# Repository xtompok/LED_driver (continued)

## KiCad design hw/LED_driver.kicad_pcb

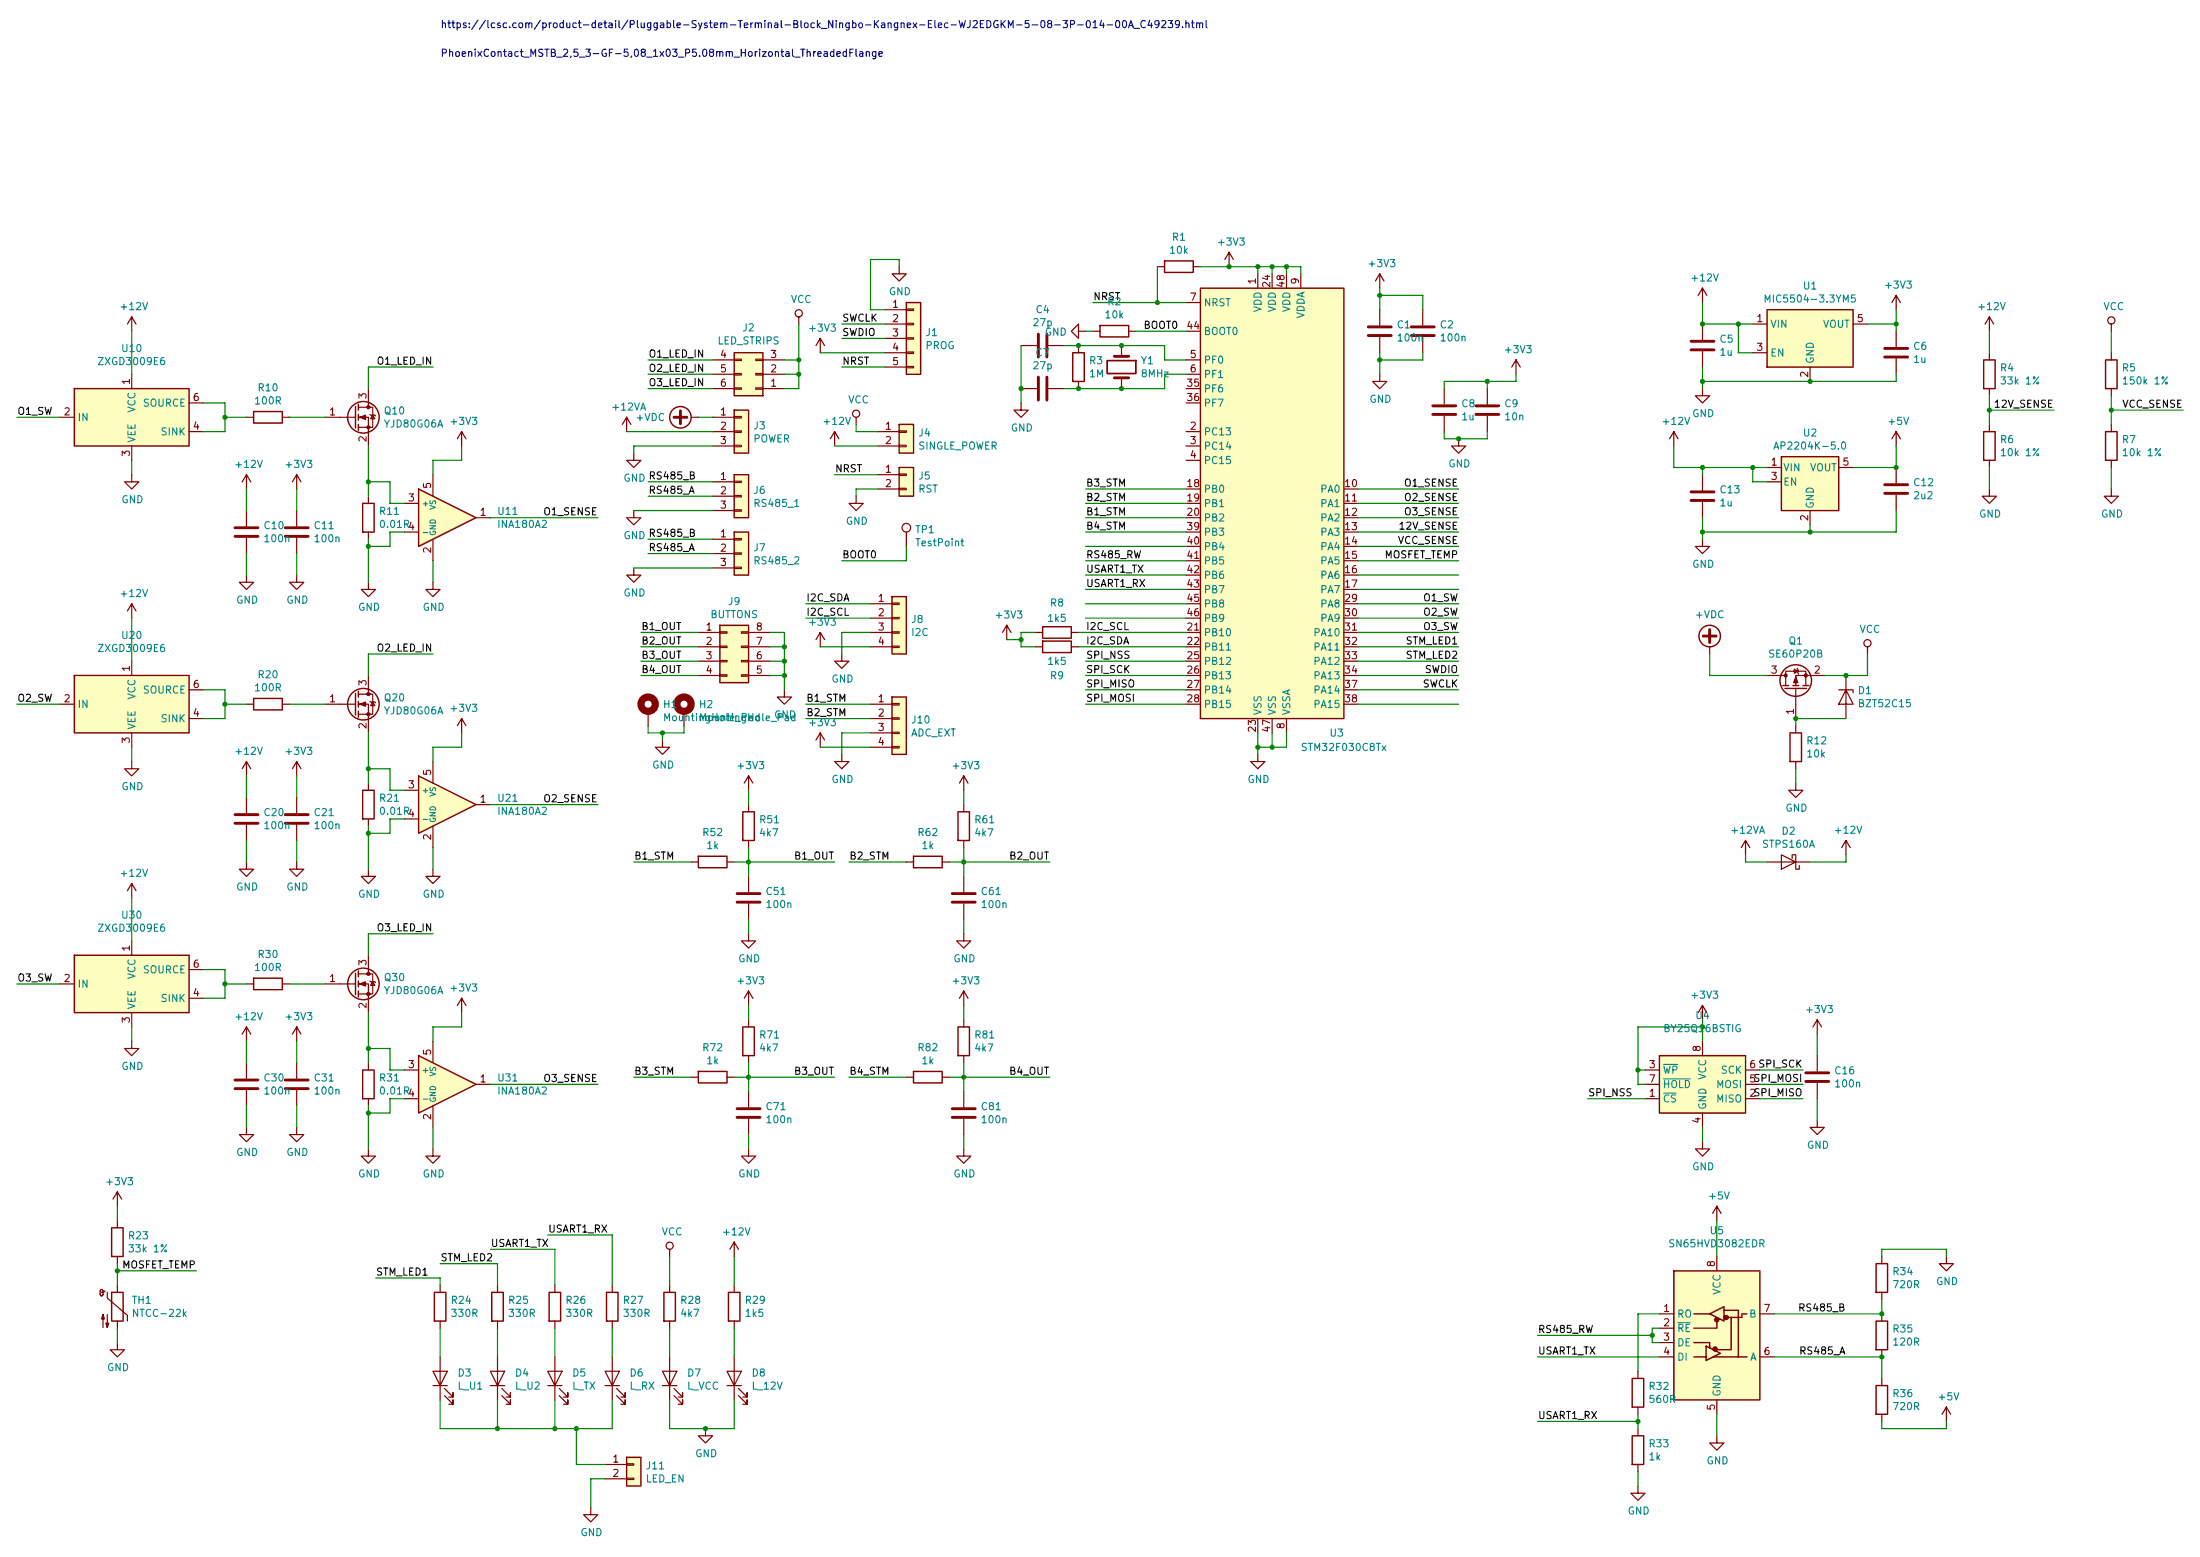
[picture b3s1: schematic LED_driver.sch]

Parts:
C1, C2, C10, C11, C16, C20, C21, C30, C31, C51, C61, C71, C81: 100n; C_0603_1608Metric
C4, C7: 27p; C_0603_1608Metric
C5, C6, C8, C13: 1u; C_0603_1608Metric
C9: 10n; C_0603_1608Metric
C12: 2u2; C_0603_1608Metric
D1: BZT52C15; D_SOD-123F
D2: STPS160A; D_SMA
D3: L_U1; LED_PLCC-2
D4: L_U2; LED_PLCC-2
D5: L_TX; LED_PLCC-2
D6: L_RX; LED_PLCC-2
D7: L_VCC; LED_PLCC-2
D8: L_12V; LED_PLCC-2
H1, H2: MountingHole_Pad; MountingHole_3.2mm_M3_Pad_Via
J1: PROG; Molex_KK-254_AE-6410-05A_1x05_P2.54mm_Vertical
J2: LED_STRIPS; Molex_Micro-Fit_3.0_43045-0600_2x03_P3.00mm_Horizontal
J3: POWER; PhoenixContact_MSTB_2,5_3-GF-5,08_1x03_P5.08mm_Horizontal_T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
J4: SINGLE_POWER; PinHeader_1x02_P2.54mm_Vertical
J5: RST; PinHeader_1x02_P2.54mm_Vertical
J6: RS485_1; PTSA_1.5_3-3.5-Z_1985205
J7: RS485_2; PTSA_1.5_3-3.5-Z_1985205
J8: I2C; Molex_KK-254_AE-6410-04A_1x04_P2.54mm_Vertical
J9: BUTTONS; Molex_Micro-Fit_3.0_43045-0800_2x04_P3.00mm_Horizontal
J10: ADC_EXT; Molex_KK-254_AE-6410-04A_1x04_P2.54mm_Vertical
J11: LED_EN; PinHeader_1x02_P2.54mm_Vertical
Q1: SE60P20B; TO-252-2
Q10, Q20, Q30: YJD80G06A; TO-252-2
R1, R2, R12: 10k; R_0603_1608Metric
R3: 1M; R_0603_1608Metric
R4, R23: 33k 1%; R_0603_1608Metric
R5: 150k 1%; R_0603_1608Metric
R6, R7: 10k 1%; R_0603_1608Metric
R8, R9, R29: 1k5; R_0603_1608Metric
R10, R20, R30: 100R; R_0603_1608Metric
R11, R21, R31: 0.01R; R_1206_3216Metric
R24, R25, R26, R27: 330R; R_0603_1608Metric
R28, R51, R61, R71, R81: 4k7; R_0603_1608Metric
R32: 560R; R_0603_1608Metric
R33, R52, R62, R72, R82: 1k; R_0603_1608Metric
R34, R36: 720R; R_0603_1608Metric
R35: 120R; R_0603_1608Metric
TH1: NTCC-22k; C_Disc_D3.8mm_W2.6mm_P2.50mm
TP1: TestPoint; TestPoint_THTPad_D2.0mm_Drill1.0mm
U1: MIC5504-3.3YM5; SOT-23-5
U2: AP2204K-5.0; SOT-23-5
U3: STM32F030C8Tx; LQFP-48_7x7mm_P0.5mm
U4: BY25Q16BSTIG; SOP-8_3.9x4.9mm_P1.27mm
U5: SN65HVD3082EDR; SOP-8_3.9x4.9mm_P1.27mm
U10, U20, U30: ZXGD3009E6; SOT-23-6
U11, U21, U31: INA180A2; SOT-23-5
Y1: 8MHz; Crystal_HC49-U_Vertical

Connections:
+3V3: C1.1, C2.1, C6.1, C8.1, C9.1, C11.1, C16.1, C21.1, C31.1, J1.4, J8.4, J10.4, R1.1, R8.2, R9.2, R23.1, R51.1, R61.1, R71.1, R81.1, U1.5 (VOUT), U3.1 (VDD), U3.9 (VDDA), U3.24 (VDD), U3.48 (VDD), U4.3 (~WP), U4.7 (~HOLD), U4.8 (VCC), U11.5 (VS), U21.5 (VS), U31.5 (VS)
+5V: C12.1, R36.2, U2.5 (VOUT), U5.8 (VCC)
+12V: C5.1, C10.1, C13.1, C20.1, C30.1, D2.1 (K), J4.2, R4.1, R29.1, U1.1 (VIN), U1.3 (EN), U2.1 (VIN), U2.3 (EN), U10.1 (VCC), U20.1 (VCC), U30.1 (VCC)
+12VA: D2.2 (A), J3.2
+VDC: J3.1, Q1.3 (D)
/12V_SENSE: R4.2, R6.1, U3.13 (PA3)
/B1_OUT: C51.1, J9.1, R51.2, R52.1
/B1_STM: J10.1, R52.2, U3.20 (PB2)
/B2_OUT: C61.1, J9.2, R61.2, R62.1
/B2_STM: J10.2, R62.2, U3.19 (PB1)
/B3_OUT: C71.1, J9.3, R71.2, R72.1
/B3_STM: R72.2, U3.18 (PB0)
/B4_OUT: C81.1, J9.4, R81.2, R82.1
/B4_STM: R82.2, U3.39 (PB3)
/BOOT0: R2.1, TP1.1, U3.44 (BOOT0)
/I2C_SCL: J8.2, R8.1, U3.21 (PB10)
/I2C_SDA: J8.1, R9.1, U3.22 (PB11)
/MOSFET_TEMP: R23.2, TH1.1, U3.15 (PA5)
/NRST: J1.5, J5.1, R1.2, U3.7 (NRST)
/O1_LED_IN: J2.4, Q10.3 (D)
/O1_SENSE: U3.10 (PA0), U11.1
/O1_SW: U3.29 (PA8), U10.2 (IN)
/O2_LED_IN: J2.5, Q20.3 (D)
/O2_SENSE: U3.11 (PA1), U21.1
/O2_SW: U3.30 (PA9), U20.2 (IN)
/O3_LED_IN: J2.6, Q30.3 (D)
/O3_SENSE: U3.12 (PA2), U31.1
/O3_SW: U3.31 (PA10), U30.2 (IN)
/RS485_A: J6.2, J7.2, R35.2, R36.1, U5.6 (A)
/RS485_B: J6.1, J7.1, R34.2, R35.1, U5.7 (B)
/RS485_RW: U3.41 (PB5), U5.2 (~RE), U5.3 (DE)
/SPI_MISO: U3.27 (PB14), U4.2 (MISO)
/SPI_MOSI: U3.28 (PB15), U4.5 (MOSI)
/SPI_NSS: U3.25 (PB12), U4.1 (~CS)
/SPI_SCK: U3.26 (PB13), U4.6 (SCK)
/STM_LED1: R24.1, U3.32 (PA11)
/STM_LED2: R25.1, U3.33 (PA12)
/SWCLK: J1.2, U3.37 (PA14)
/SWDIO: J1.3, U3.34 (PA13)
/USART1_RX: R27.1, R32.2, R33.1, U3.43 (PB7)
/USART1_TX: R26.1, U3.42 (PB6), U5.4 (DI)
/VCC_SENSE: R5.2, R7.1, U3.14 (PA4)
GND: C1.2, C2.2, C4.2, C5.2, C6.2, C7.2, C8.2, C9.2, C10.2, C11.2, C12.2, C13.2, C16.2, C20.2, C21.2, C30.2, C31.2, C51.2, C61.2, C71.2, C81.2, D7.1 (K), D8.1 (K), H1.1, H2.1, J1.1, J3.3, J5.2, J6.3, J7.3, J8.3, J9.5, J9.6, J9.7, J9.8, J10.3, J11.2, R2.2, R6.2, R7.2, R11.2, R12.2, R21.2, R31.2, R33.2, R34.1, TH1.2, U1.2 (GND), U2.2 (GND), U3.8 (VSSA), U3.23 (VSS), U3.47 (VSS), U4.4 (GND), U5.5 (GND), U10.3 (VEE), U11.2 (GND), U11.4 (-), U20.3 (VEE), U21.2 (GND), U21.4 (-), U30.3 (VEE), U31.2 (GND), U31.4 (-)
unnamed: C4.1, R3.1, U3.5 (PF0), Y1.1
unnamed: C7.1, R3.2, U3.6 (PF1), Y1.2
unnamed: D1.2 (A), Q1.1 (G), R12.1
unnamed: D3.1 (K), D4.1 (K), D5.1 (K), D6.1 (K), J11.1
unnamed: D3.2 (A), R24.2
unnamed: D4.2 (A), R25.2
unnamed: D5.2 (A), R26.2
unnamed: D6.2 (A), R27.2
unnamed: D7.2 (A), R28.2
unnamed: D8.2 (A), R29.2
unnamed: Q10.1 (G), R10.1
unnamed: Q10.2 (S), R11.1, U11.3 (+)
unnamed: Q20.1 (G), R20.1
unnamed: Q20.2 (S), R21.1, U21.3 (+)
unnamed: Q30.1 (G), R30.1
unnamed: Q30.2 (S), R31.1, U31.3 (+)
unnamed: R10.2, U10.4 (SINK), U10.6 (SOURCE)
unnamed: R20.2, U20.4 (SINK), U20.6 (SOURCE)
unnamed: R30.2, U30.4 (SINK), U30.6 (SOURCE)
unnamed: R32.1, U5.1 (RO)
VCC: D1.1 (K), J2.1, J2.2, J2.3, J4.1, Q1.2 (S), R5.1, R28.1

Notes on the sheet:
https://lcsc.com/product-detail/Pluggable-System-Terminal-Block_Ningbo-Kangnex-Elec-WJ2EDGKM-5-08-3P-014-00A_C49239.html
PhoenixContact_MSTB_2,5_3-GF-5,08_1x03_P5.08mm_Horizontal_ThreadedFlange

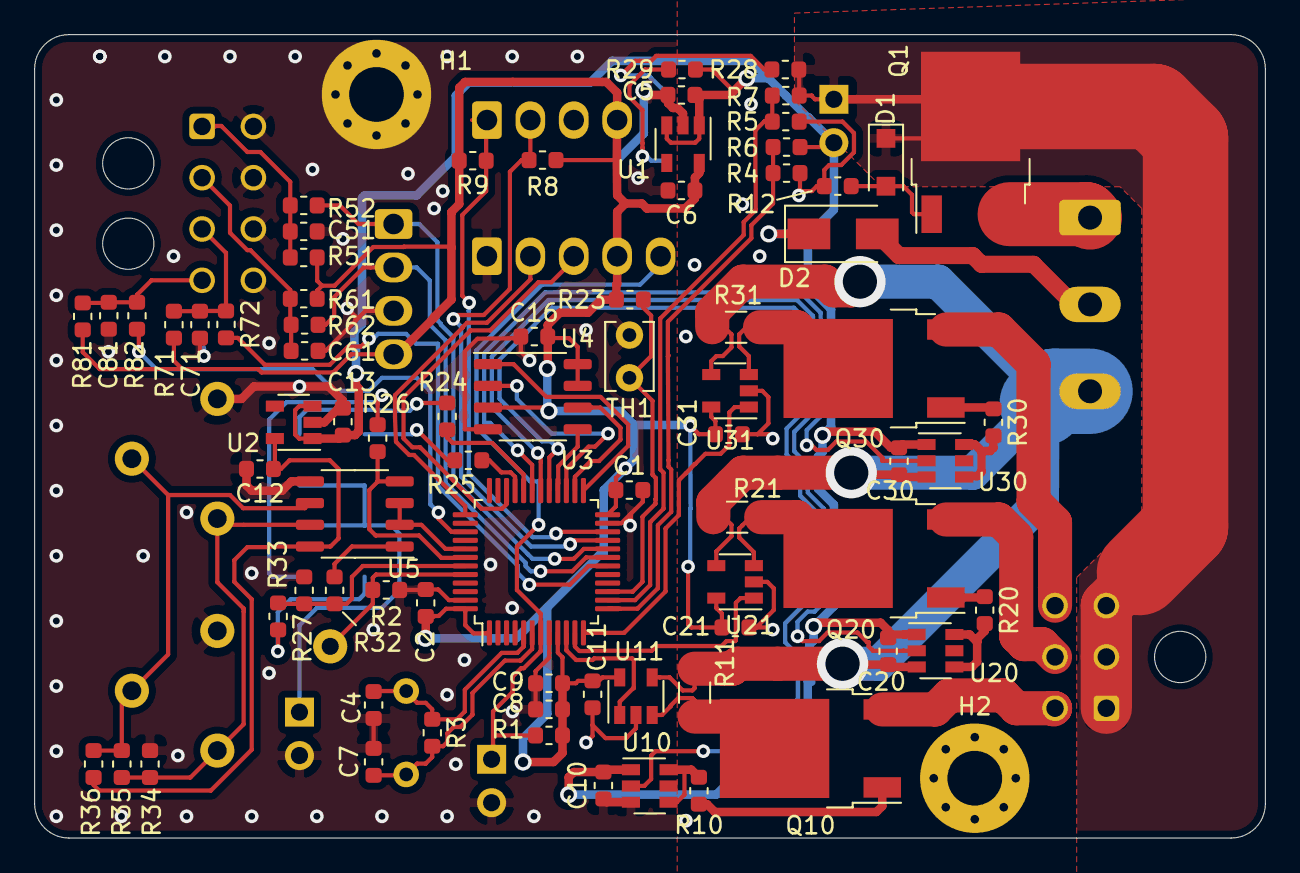
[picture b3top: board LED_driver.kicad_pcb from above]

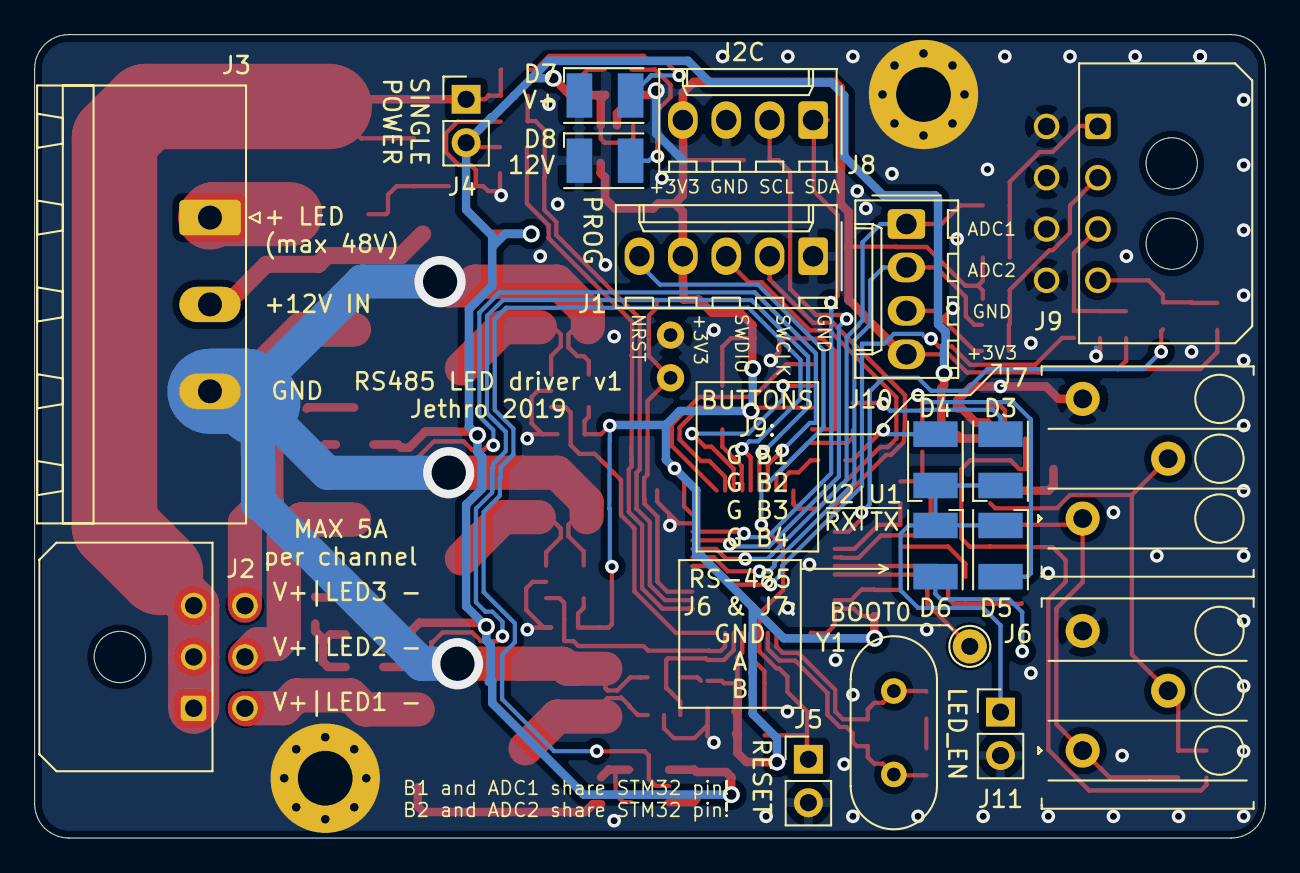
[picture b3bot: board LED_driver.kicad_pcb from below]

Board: 2 copper layers, 72.0 x 47.0 mm, 96 parts (19 on the bottom side), 64 nets.

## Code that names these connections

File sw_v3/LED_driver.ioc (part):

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Mcu.Name=STM32G070CBTx
Mcu.Package=LQFP48
Mcu.UserName=STM32G070CBTx
PA0.Mode=IN0
PA0.Signal=ADC1_IN0
PA1.Mode=IN1
PA1.Signal=ADC1_IN1
PA11\ [PA9].Mode=I2C
PA11\ [PA9].Signal=I2C2_SCL
PA12\ [PA10].Mode=I2C
PA12\ [PA10].Signal=I2C2_SDA
PA13.Mode=Serial_Wire
PA13.Signal=SYS_SWDIO
PA14-BOOT0.Mode=Serial_Wire
PA14-BOOT0.Signal=SYS_SWCLK
PA2.Mode=IN2
PA2.Signal=ADC1_IN2
PA6.Signal=S_TIM3_CH1
PA7.Signal=S_TIM3_CH2
PA8.Signal=S_TIM1_CH1
PA9.Signal=S_TIM1_CH2
PB0.Signal=S_TIM3_CH3
PB1.Mode=Hardware Flow Control (RS485)
PB1.Signal=USART3_DE
PB10.Mode=Asynchronous
PB10.Signal=USART3_TX
PB11.Mode=Asynchronous
PB11.Signal=USART3_RX
PB14.Signal=GPIO_Input
PB15.Signal=GPIO_Input
PB6.Mode=Asynchronous
PB6.Signal=USART1_TX
PB7.Mode=Asynchronous
PB7.Signal=USART1_RX
PB8.Signal=GPIO_Output
PB9.Signal=GPIO_Output
PC6.Signal=GPIO_Input
PF0-OSC_IN\ (PF0).Mode=HSE-External-Oscillator
PF0-OSC_IN\ (PF0).Signal=RCC_OSC_IN
PF1-OSC_OUT\ (PF1).Mode=HSE-External-Oscillator
PF1-OSC_OUT\ (PF1).Signal=RCC_OSC_OUT
RCC.HSE_VALUE=16000000
RCC.SYSCLKFreq_VALUE=64000000
RCC.SYSCLKSource=RCC_SYSCLKSOURCE_PLLCLK
board=custom

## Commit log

2020-01-03 First version of LED driver.
2020-03-21 Prototype version v1.
2021-04-25 Second version of the driver.
2021-04-25 Finalization.
2021-05-24 Added testing firmware with working ADC.
2021-05-26 Working ADC DMA.
2022-01-14 Information from debugging (czech).
2022-05-15 First alpha of Modbus using code.
2023-01-08 First version of production SW.
2024-09-14 Added schematic and started placement for 3rd version.
2024-09-16 Routed.
2024-09-17 Silkscreen finished, bugfixes.
2024-10-05 Added LCSC numbers.
2024-11-06 Updated .ioc file
2024-11-06 First compilable (untested) version.
